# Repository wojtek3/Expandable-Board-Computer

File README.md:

# Board Computer display board

## General info
This project is a display for simple board computer dedicated for odl cars which didn't have it.

## Base features
* ST7789 display
* EGT from K-type thermocouple
* AFR from analog input
* Control buttons
* I2C bus for more modules

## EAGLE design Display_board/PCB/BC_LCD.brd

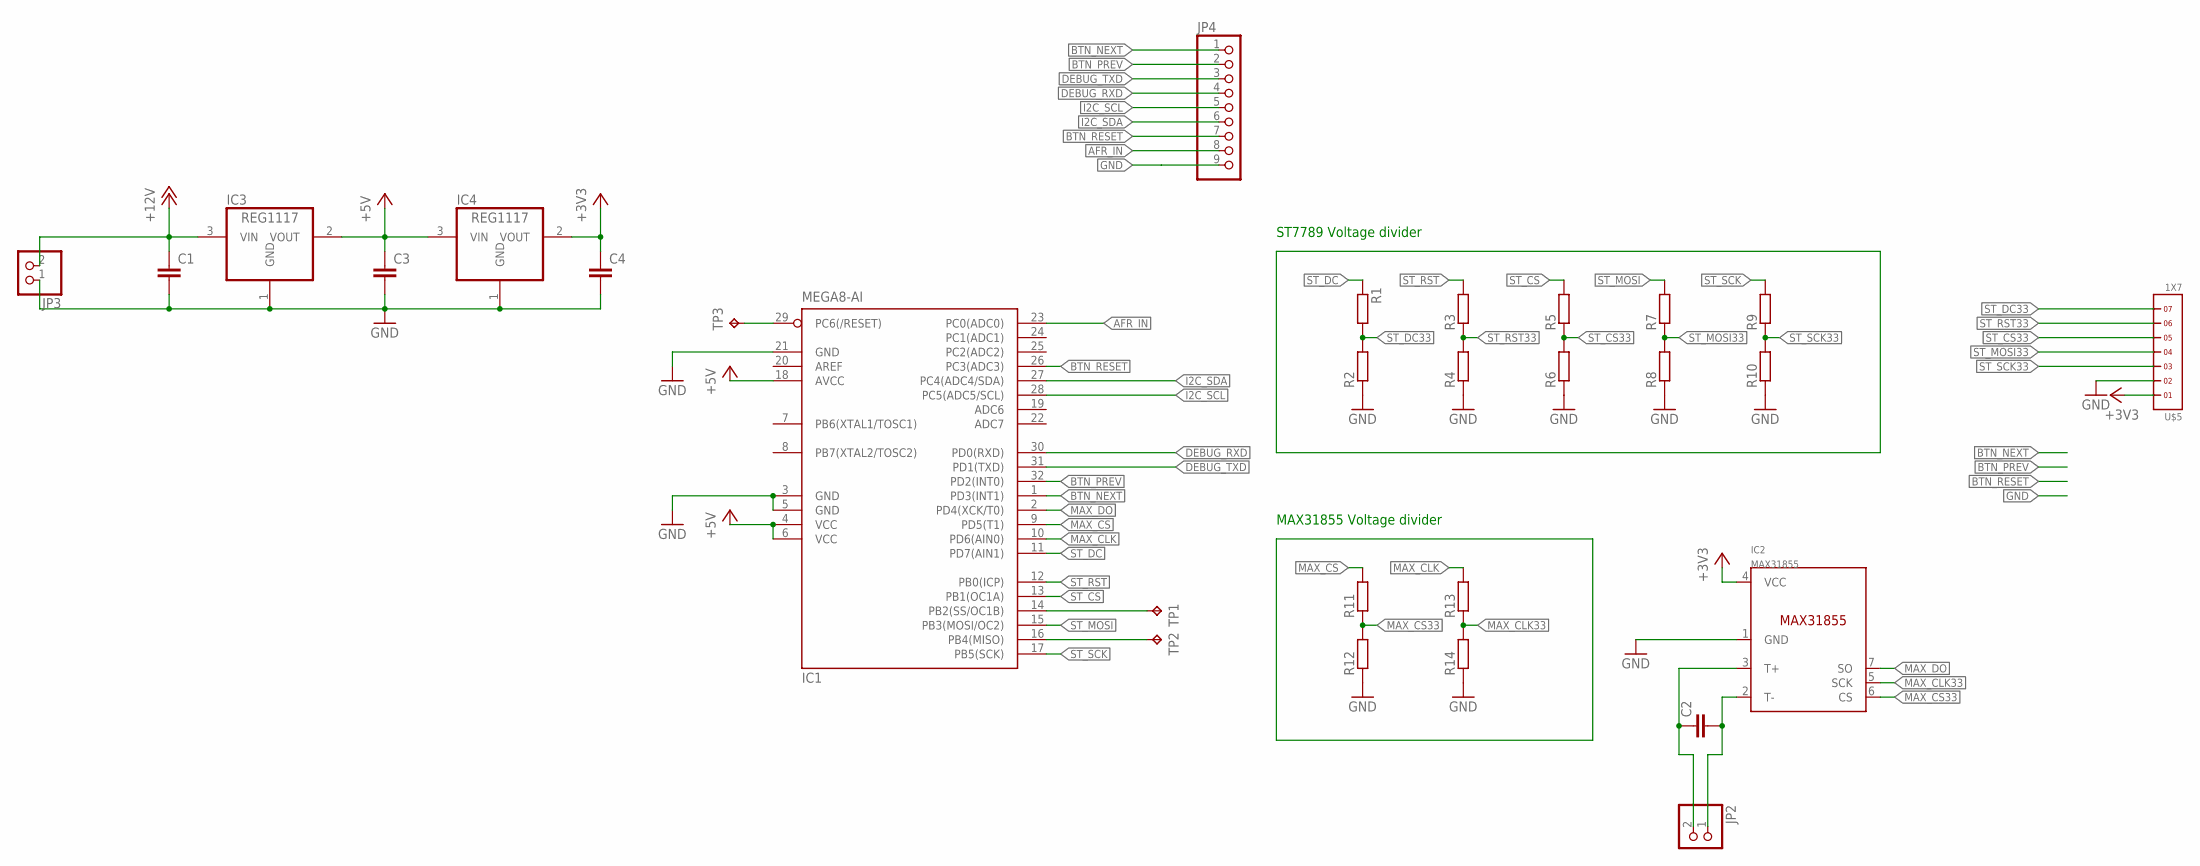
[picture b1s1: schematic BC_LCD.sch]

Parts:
C1, C2, C3, C4: C-EUC0805K; C0805K
IC1: MEGA8-AI; TQFP32-08
IC2: MAX31855; SOIC8
IC3, IC4: REG1117; SOT223
JP2, JP3: PINHD-1X2; 1X02
JP4: PINHD-1X9; 1X09
R1, R2, R3, R4, R5, R6, R7, R8, R9, R10, R11, R12, R13, R14: R-EU_M0805; M0805
TP1, TP2, TP3: TPTP12R; TP12R
U$5: 1X7

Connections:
+3V3: C4.1, IC2.4 (VCC), IC4.2 (VOUT), U$5.1
+5V: C3.1, IC1.4 (VCC), IC1.6 (VCC), IC1.18 (AVCC), IC3.2 (VOUT), IC4.3 (VIN)
+12V: C1.1, IC3.3 (VIN), JP3.2
AFR_IN: IC1.23 (PC0(ADC0)), JP4.8
BTN_NEXT: IC1.1 (PD3(INT1)), JP4.1
BTN_PREV: IC1.32 (PD2(INT0)), JP4.2
BTN_RESET: IC1.26 (PC3(ADC3)), JP4.7
DEBUG_RXD: IC1.30 (PD0(RXD)), JP4.4
DEBUG_TXD: IC1.31 (PD1(TXD)), JP4.3
GND: C1.2, C3.2, C4.2, IC1.3 (GND), IC1.5 (GND), IC1.21 (GND), IC2.1 (GND), IC3.1 (GND), IC4.1 (GND), JP3.1, JP4.9, R2.1, R4.1, R6.1, R8.1, R10.1, R12.1, R14.1, U$5.2
I2C_SCL: IC1.28 (PC5(ADC5/SCL)), JP4.5
I2C_SDA: IC1.27 (PC4(ADC4/SDA)), JP4.6
MAX_CLK: IC1.10 (PD6(AIN0)), R13.2
MAX_CLK33: IC2.5 (SCK), R13.1, R14.2
MAX_CS: IC1.9 (PD5(T1)), R11.2
MAX_CS33: IC2.6 (CS), R11.1, R12.2
MAX_DO: IC1.2 (PD4(XCK/T0)), IC2.7 (SO)
unnamed: C2.1, IC2.3 (T+), JP2.2
unnamed: C2.2, IC2.2 (T-), JP2.1
unnamed: IC1.14 (PB2(SS/OC1B)), TP1.TP
unnamed: IC1.16 (PB4(MISO)), TP2.TP
unnamed: IC1.29 (PC6(/RESET)), TP3.TP
ST_CS: IC1.13 (PB1(OC1A)), R5.2
ST_CS33: R5.1, R6.2, U$5.5
ST_DC: IC1.11 (PD7(AIN1)), R1.1
ST_DC33: R1.2, R2.2, U$5.7
ST_MOSI: IC1.15 (PB3(MOSI/OC2)), R7.2
ST_MOSI33: R7.1, R8.2, U$5.4
ST_RST: IC1.12 (PB0(ICP)), R3.2
ST_RST33: R3.1, R4.2, U$5.6
ST_SCK: IC1.17 (PB5(SCK)), R9.2
ST_SCK33: R9.1, R10.2, U$5.3

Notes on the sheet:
ST7789 Voltage divider
MAX31855 Voltage divider

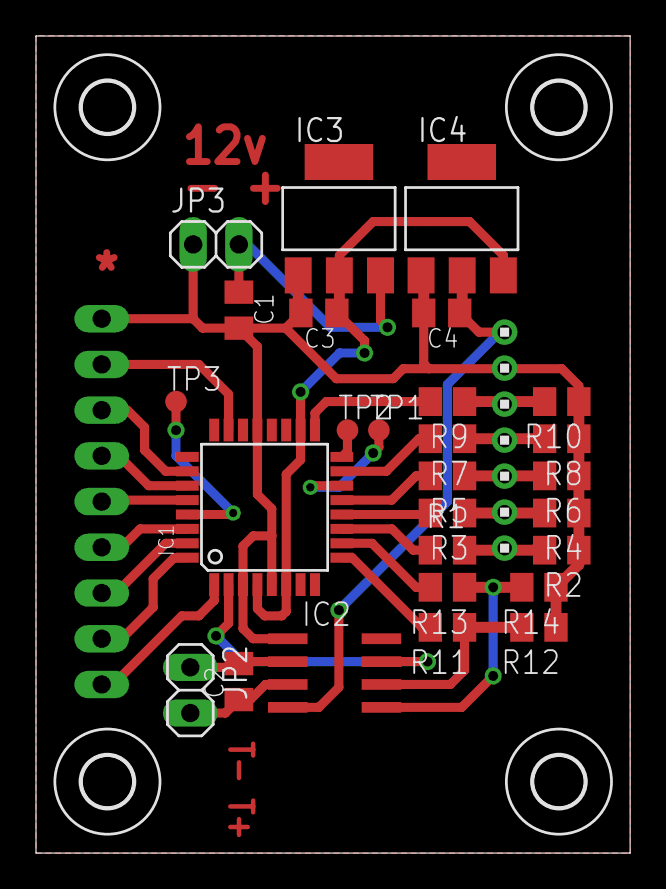
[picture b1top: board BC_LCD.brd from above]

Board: 2 copper layers, 33.0 x 45.4 mm, 33 parts (1 on the bottom side), 32 nets.

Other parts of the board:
U$1, U$2, U$3, U$4: 2,8

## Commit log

2021-11-12 init
2021-11-12 add PCB
2021-11-12 reset and pb/lpg
